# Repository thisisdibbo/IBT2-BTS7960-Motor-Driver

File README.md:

# IBT-2 High-Current H-Bridge Motor Driver (BTS7960B) — Custom PCB

A custom-designed **IBT-2 style H-bridge motor driver** built around two Infineon **BTS7960B** high-current half-bridges and a **TI SN74HC244** input buffer. It drives one brushed DC motor in both directions, with PWM speed control from any microcontroller (Arduino, ESP32, STM32, …).

The board was designed in Autodesk EAGLE, then fabricated, assembled and bench-tested: **at full drive, the voltage across the motor terminals equals the supply voltage**, confirming that the H-bridge switches the full supply onto the load.

It also has a **built-in HAT circuit**: a red power LED, two green signal LEDs and a 4-pin JST connector that plugs straight into an Arduino shield PCB — see [Built-in HAT Circuit](#built-in-hat-circuit).

## Contents

- [Fabricated Board](#fabricated-board)
- [Schematic and PCB](#schematic-and-pcb)
- [Features](#features)
- [Built-in HAT Circuit](#built-in-hat-circuit)
- [How It Works](#how-it-works)
- [Pinout](#pinout)
- [Control Logic](#control-logic)
- [Quick Start (Arduino)](#quick-start-arduino)
- [Specifications](#specifications)
- [Test Results](#test-results)
- [Bill of Materials](#bill-of-materials)
- [Repository Structure](#repository-structure)
- [Limitations and Future Improvements](#limitations-and-future-improvements)
- [References](#references)
- [Author](#author)
- [License](#license)

---

## Fabricated Board

<!-- Put your two photos in the images/ folder with exactly these names: fabricated_1.jpg and fabricated_2.jpg -->
<p align="center">
  
  &nbsp;&nbsp;
  
</p>
<p align="center"><em>The fabricated and assembled board</em></p>

## Schematic and PCB

<p align="center"><em>Schematic — U4 buffers the inputs, U2 + U3 form the H-bridge, J1 = power in, J2 = motor out</em></p>

<p align="center"><em>PCB layout — 2 layers, 59.6 × 52.3 mm, red = top copper, blue = bottom copper, GND pour on both layers</em></p>

## Features

- **Full H-bridge** from two BTS7960B NovalithIC™ half-bridges (7 mΩ high-side + 9 mΩ low-side, typ.)
- **Buffered inputs** — an SN74HC244 sits between the microcontroller and the power stage
- **Only two control signals** (RPWM, LPWM) — both half-bridges are enabled automatically when logic power is present
- **Safe default state** — on-board 30 kΩ pull-downs hold RPWM/LPWM LOW if the MCU pins float (e.g. during reset), so the motor is held in brake instead of running
- **Built-in HAT circuit** — red power LED, two green signal LEDs and a 4-pin JST connector for direct connection to an Arduino shield PCB
- **Protection built into the BTS7960B** — current limitation, short-circuit and over-temperature shutdown, under-voltage shutdown, over-voltage lock-out
- **Adjustable slew rate** through the SR resistors (10 kΩ fitted)
- **Bulk capacitor** on the motor supply and a decoupling capacitor on the logic supply
- **5 mm screw terminals** for power and motor
- 4 × Ø3 mm mounting holes

## Built-in HAT Circuit

The logic side of the board is a small built-in **HAT circuit**: the driver plugs into an Arduino shield PCB with one cable, and its status can be read at a glance — no loose jumper wires.

| Part | Type | Function |
|:---:|:---|:---|
| LD1 | 🔴 Red LED, 3 mm | **Power ON** — lights when the logic supply (VCC) is present |
| R1 | Diode (on the R1 footprint) | **Reverse protection** — in series with the red power LED, protects the LED branch if VCC is connected backwards |
| LD2 | 🟢 Green LED, 3 mm | **RPWM signal** — lights when RPWM is HIGH (forward) |
| LD3 | 🟢 Green LED, 3 mm | **LPWM signal** — lights when LPWM is HIGH (reverse) |
| X1 | 4-pin JST connector | **Direct connection to the Arduino shield PCB** with a single JST cable (VCC, LPWM, RPWM, GND) |

The green LEDs are driven by the control signals themselves, so under PWM their brightness follows the duty cycle — direction and approximate speed are visible at a glance.

## How It Works

```mermaid
flowchart LR
    MCU["Arduino shield PCB<br/>or any MCU"] -->|RPWM, LPWM| X1["HAT circuit<br/>JST connector + LEDs"]
    X1 --> BUF["U4 · SN74HC244<br/>input buffer"]
    BUF -->|IN, INH| U2["U2 · BTS7960B<br/>half-bridge A"]
    BUF -->|IN, INH| U3["U3 · BTS7960B<br/>half-bridge B"]
    PSU["Motor supply<br/>B+ / B−"] --> U2
    PSU --> U3
    U2 -->|M+| MOT(("DC<br/>motor"))
    U3 -->|M−| MOT
```

- **Power stage** — each BTS7960B contains a high-side P-MOSFET, a low-side N-MOSFET and a gate driver with built-in dead-time. With INH HIGH, `IN = HIGH` connects the output to B+ and `IN = LOW` connects it to GND; INH LOW puts the chip to sleep. U2 drives **M+**, U3 drives **M−**, and the motor sits between them.
- **Input stage** — U4 buffers RPWM → U2 `IN` and LPWM → U3 `IN`. Two more U4 channels (1A2, 1A4) are tied to VCC, so both `INH` pins go HIGH as soon as logic power is applied. The unused second half of U4 has its inputs and output-enable tied to GND so nothing floats.
- **Slew rate and current sense** — R9/R11 (10 kΩ, SR → GND) give a moderate switching slew rate. The IS (current-sense / fault) pins are terminated with R10/R12 (10 kΩ) to GND and are not routed to the header in this revision.
- **Supply** — C2 (330 µF) is the bulk capacitor on B+, C1 (100 nF) decouples U4. A diode on the R1 footprint sits in series with the power-LED branch (X1-1 → R1 → R2 → LD1). Logic ground and power ground are the same net.

## Pinout

> The **B+ B− M+ M−** labels are printed on the **bottom** silkscreen. On X1, pin 4 (GND) is next to the **GND** mark on the top silkscreen.

### X1 — JST logic connector (4-pin, to the Arduino shield)

| Pin | Signal | Description |
|:---:|:---|:---|
| 1 | **VCC** | Logic supply for U4 — 5 V (or 3.3 V for 3.3 V MCUs). Also enables both half-bridges; red LED LD1 lights. |
| 2 | **LPWM** | Drives U3 → **M−**. HIGH = M− to B+, LOW = M− to GND. Green LED: LD3 |
| 3 | **RPWM** | Drives U2 → **M+**. HIGH = M+ to B+, LOW = M+ to GND. Green LED: LD2 |
| 4 | **GND** | Ground (same net as B−) |

### J1 — Power input (2-pin screw terminal, 5 mm)

| Pin | Label | Description |
|:---:|:---:|:---|
| 1 | **B+** | Motor supply V<sub>S</sub>, 5.5 – 27.5 V |
| 2 | **B−** | Supply ground |

### J2 — Motor output (2-pin screw terminal, 5 mm)

| Pin | Label | Description |
|:---:|:---:|:---|
| 1 | **M+** | Output of U2 (controlled by RPWM) |
| 2 | **M−** | Output of U3 (controlled by LPWM) |

> **Wiring:** always connect the microcontroller GND to X1-4. B− and X1-4 are the same ground.

## Control Logic

Both half-bridges are enabled whenever VCC is present (INH = HIGH).

| RPWM (X1-3) | LPWM (X1-2) | M+ | M− | Motor |
|:---:|:---:|:---:|:---:|:---|
| HIGH | LOW | B+ | GND | Forward, full speed (V<sub>out</sub> ≈ V<sub>in</sub>) |
| LOW | HIGH | GND | B+ | Reverse, full speed |
| PWM | LOW | PWM | GND | Forward, speed ∝ duty cycle |
| LOW | PWM | GND | PWM | Reverse, speed ∝ duty cycle |
| LOW | LOW | GND | GND | Brake (both low-side switches on) — also the default when the inputs float |
| HIGH | HIGH | B+ | B+ | Brake (both high-side switches on) |

> Bring the motor to a stop (both inputs LOW) before reversing direction.

## Quick Start (Arduino)

Plug the JST cable from the Arduino shield PCB into X1, or wire the pins directly:

| Driver | Connect to |
|:---|:---|
| X1-1 VCC | Arduino **5V** |
| X1-2 LPWM | Arduino **D6** |
| X1-3 RPWM | Arduino **D5** |
| X1-4 GND | Arduino **GND** |
| J1 B+ / B− | Motor power supply + / − |
| J2 M+ / M− | DC motor |

```cpp
// IBT-2 (BTS7960B) custom driver — bidirectional test
const uint8_t RPWM = 5;   // X1-3 -> M+
const uint8_t LPWM = 6;   // X1-2 -> M-

// speed: -255 (full reverse) ... 0 (brake) ... +255 (full forward)
void setMotor(int speed) {
  speed = constrain(speed, -255, 255);
  if (speed >= 0) {
    analogWrite(LPWM, 0);
    analogWrite(RPWM, speed);
  } else {
    analogWrite(RPWM, 0);
    analogWrite(LPWM, -speed);
  }
}

void setup() {
  pinMode(RPWM, OUTPUT);
  pinMode(LPWM, OUTPUT);
  setMotor(0);
}

void loop() {
  setMotor(255);  delay(2000);   // full forward: V(M+ - M-) ≈ +V_in
  setMotor(0);    delay(1000);   // brake
  setMotor(-255); delay(2000);   // full reverse: V(M+ - M-) ≈ -V_in
  setMotor(0);    delay(1000);
  setMotor(128);  delay(2000);   // about 50 % speed forward
  setMotor(0);    delay(1000);
}
```

**Notes**

- **3.3 V boards (ESP32, STM32, Pico):** power X1-1 (VCC) from **3.3 V**, not 5 V. With VCC = 5 V the 74HC244 needs about 3.5 V for a logic HIGH, which a 3.3 V pin may not reach reliably. The BTS7960B inputs only need ≥ 2.15 V, so 3.3 V logic is enough. *(3.3 V operation follows from the datasheets; not yet tested on this board.)*
- **Never power VCC above 5.3 V** — U4 passes VCC straight to the BTS7960B `IN`/`INH` pins, whose absolute maximum is 5.3 V.
- Arduino Uno PWM on D5/D6 runs at about 980 Hz, which can make the motor whine. The BTS7960B supports PWM up to 25 kHz.

## Specifications

| Parameter | Value |
|:---|:---|
| Motor supply V<sub>S</sub> (B+) | 5.5 – 27.5 V (BTS7960B operating range; undervoltage shutdown at 4.0 – 5.4 V, over-voltage lock-out at 27.6 – 30 V) |
| Logic supply (VCC) | 5 V nominal, 3.3 V for 3.3 V MCUs — max 5.3 V |
| Control inputs | RPWM, LPWM — active HIGH, 30 kΩ pull-down on each |
| Interface (HAT circuit) | 4-pin JST connector · red power LED · 2 green signal LEDs |
| PWM frequency | Up to 25 kHz |
| Switch on-resistance | 7 mΩ high-side + 9 mΩ low-side (typ. at 25 °C) → 16 mΩ path resistance |
| IC current limit | 43 A typ. — *board current is limited by the copper, see [Limitations](#limitations-and-future-improvements)* |
| Protection | Current limitation, short-circuit, over-temperature (latched), under-/over-voltage |
| PCB | 2 layers, 59.6 × 52.3 mm, 35 µm (1 oz) copper, GND pour on top and bottom |
| Trace widths | Signals 0.51 mm · V<sub>S</sub> 0.76–0.81 mm · motor outputs 1.27 mm |
| Mounting | 4 × Ø3.0 mm holes |
| Design tool | Autodesk EAGLE 9.6.2 |

## Test Results

| Test | Condition | Result |
|:---|:---|:---|
| Output voltage at full drive | Motor supply on B+/B−, logic powered, one input HIGH and the other LOW | V<sub>M+ − M−</sub> = V<sub>in</sub> ✅ |

<!-- Add your measured numbers here, e.g. "12.0 V in -> 12.0 V out", plus the motor or load used. -->

The output matched the supply, which means the high-side switch of one BTS7960B and the low-side switch of the other are fully on. The only loss is the typical 16 mΩ path resistance (≈ 16 mV per amp of motor current).

## Bill of Materials

| Ref | Qty | Value / Part | Package | Function |
|:---|:---:|:---|:---|:---|
| U2, U3 | 2 | Infineon **BTS7960B** | P-TO-263-7 | High-current half-bridge |
| U4 | 1 | TI **SN74HC244DW** | SOIC-20 (wide) | Octal buffer, input stage |
| R9, R11 | 2 | 10 kΩ (103) | 1206 | Slew-rate resistor, SR → GND |
| R10, R12 | 2 | 10 kΩ (103) | 1206 | Current-sense load, IS → GND |
| R5, R8 | 2 | 30 kΩ (303) | 1206 | Pull-downs on RPWM / LPWM |
| R6, R7 | 2 | 30 kΩ (303) | 1206 | Pull-downs on U4 enable inputs (tied to VCC in this revision, so optional) |
| R1 | 1 | Diode (fitted on the R1 footprint) | THT, 7.62 mm pitch | Reverse-polarity protection for the power-LED branch (X1-1 → R1 → R2 → LD1) |
| R2, R3, R4 | 3 | 1 kΩ | THT 0207, 7.62 mm pitch | LED series resistors: R2 → LD1 (red), R3 → LD2 (green), R4 → LD3 (green) |
| LD1 | 1 | Red LED, 3 mm | THT | Power indicator (HAT circuit) |
| LD2, LD3 | 2 | Green LED, 3 mm | THT | RPWM / LPWM signal indicators (HAT circuit) |
| C1 | 1 | 100 nF ceramic (X7R, ≥ 16 V) | 1206 | U4 supply decoupling |
| C2 | 1 | 330 µF electrolytic | Radial, 5 mm pitch, up to Ø10 mm | Motor-supply bulk capacitor — voltage rating must be above B+ (e.g. 35 V for a 24 V supply) |
| X1 | 1 | 4-pin JST connector | 2.54 mm pitch (Molex 22-23-2041 footprint) | Logic connector to the Arduino shield (HAT circuit) |
| J1, J2 | 2 | 2-pin PCB screw terminal | 5 mm pitch | Power input / motor output |

> The BTS7960B is listed as obsolete by major distributors (e.g. DigiKey) — check availability before building one.

## Repository Structure

```
IBT2-BTS7960-Motor-Driver/
├── hardware/
│   ├── IBT2_BTS7960.sch            # EAGLE schematic
│   ├── IBT2_BTS7960.brd            # EAGLE board layout
│   └── IBT2_BTS7960.dxf            # DXF export (top copper, pads, vias, outline)
├── fabrication/
│   ├── board_print_2025-07-05.pdf  # 1:1 board print, A4
│   └── board_print_2025-07-06.pdf  # 1:1 board print, A4
├── images/
│   ├── schematic.png
│   ├── pcb_layout.png
│   ├── fabricated_1.jpg
│   └── fabricated_2.jpg
├── LICENSE
└── README.md
```

Open the `.sch` / `.brd` pair in **Autodesk EAGLE 9.x** or **Autodesk Fusion Electronics**; KiCad can also import EAGLE projects. Keep both files in the same folder with the same name so the schematic and board stay linked.

## Limitations and Future Improvements

**Current capability.** The BTS7960B itself handles tens of amps, but on this PCB the motor current flows through 0.76 mm (V<sub>S</sub>) and 1.27 mm (output) traces on 1 oz copper, with single vias where the power paths change layers. A rough IPC-2221 estimate puts the V<sub>S</sub> trace at about **2 – 2.7 A continuous** (10 – 20 °C temperature rise). Use it with small-to-medium motors and check the trace temperature before running higher currents.

**Fault reset.** Because `INH` is tied HIGH through U4, a latched over-temperature or short-circuit shutdown is cleared by power-cycling VCC (this pulls `INH` LOW).

Planned for the next revision:

- [ ] Replace the V<sub>S</sub> and output traces with wide copper pours and stitching vias; add more copper under the BTS7960B tabs, or a heatsink
- [ ] Add a 470 nF ceramic capacitor from V<sub>S</sub> to GND next to each BTS7960B (recommended in the datasheet)
- [ ] Bring R_IS / L_IS (current sense and fault flag) to the header, with R<sub>IS</sub> ≈ 1 kΩ (≈ 1 V per 8.5 A)
- [ ] Bring R_EN / L_EN to the header so the MCU can disable the bridge and reset faults
- [ ] Add reverse-polarity protection on B+
- [ ] Move the reverse-protection diode (now on the R1 footprint) in series with the whole VCC input — today it protects only the power-LED branch, because U4 takes VCC directly from X1-1 (a Schottky diode keeps the drop low)

## References

- [Infineon BTS7960 datasheet](https://www.infineon.com/dgdl/Infineon-BTS7960-DS-v01_01-en.pdf)
- [TI SN74HC244 product page and datasheet](https://www.ti.com/product/SN74HC244)

## Author

**Md. Mahin Rahman** — [@thisisdibbo](https://github.com/thisisdibbo) · [mr.d2003feb@gmail.com](mailto:mr.d2003feb@gmail.com)<br>
Department of Electrical and Electronic Engineering, Islamic University of Technology (IUT), Gazipur, Bangladesh

## License

Released under the [MIT License](LICENSE).

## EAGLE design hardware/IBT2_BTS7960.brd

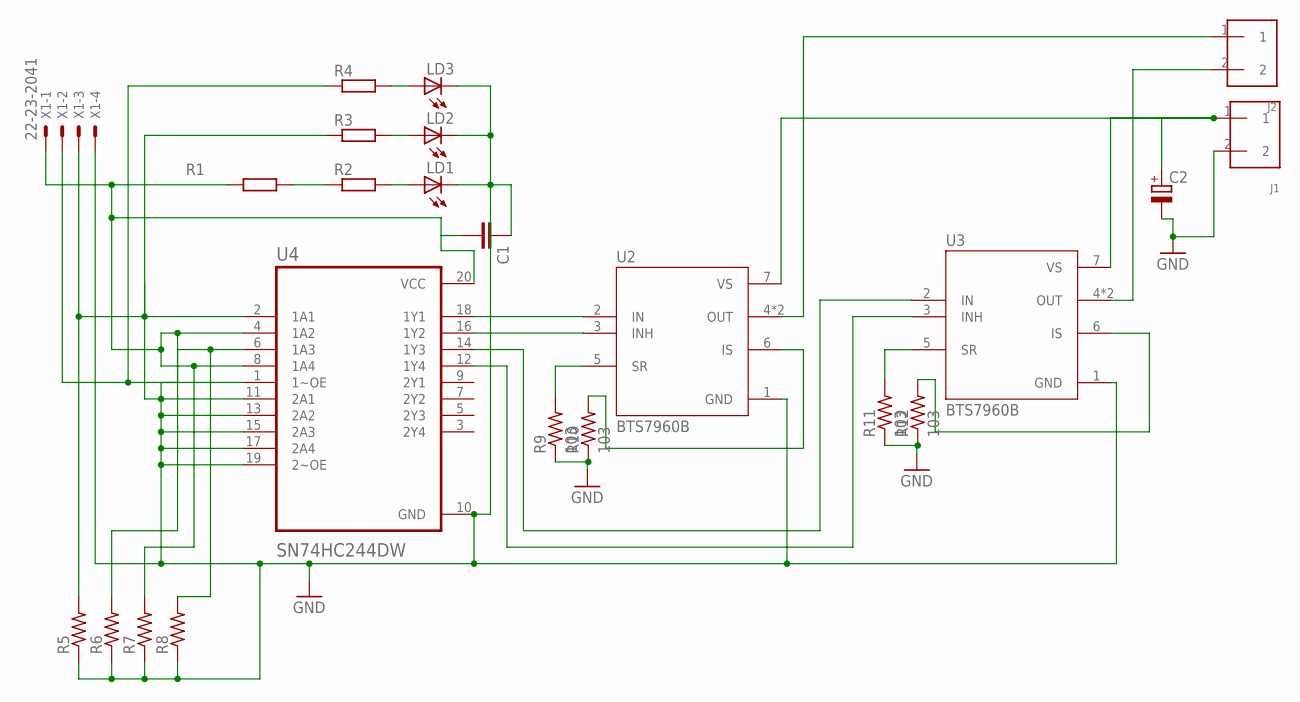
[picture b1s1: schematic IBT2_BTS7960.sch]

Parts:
C1: C-EUC1206K; C1206K
C2: CPOL-EUE5-10.5; E5-10,5
J1, J2: SCREW_TERMINAL; PHEONIX-1935161
LD1, LD2, LD3: LED3MM
R1, R2, R3, R4: R-EU_0207/7; 0207/7
R5, R6, R7, R8: R-US_M1206; M1206
R9, R10, R11, R12: 103; M1206
U2, U3: BTS7960B; DPAK127P1490X440-8N
U4: SN74HC244DW; SOIC127P1030X265-20N
X1: 22-23-2041

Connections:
GND: C1.1, C2.-, J1.2, LD1.K (C), LD2.K (C), LD3.K (C), R5.1, R6.1, R7.1, R8.1, R9.1, R10.1, R11.1, R12.1, U2.1 (GND), U3.1 (GND), U4.1 (1~OE), U4.10 (GND), U4.11 (2A1), U4.13 (2A2), U4.15 (2A3), U4.17 (2A4), U4.19 (2~OE), X1.4
unnamed: U2.2 (IN), U4.18 (1Y1)
unnamed: R1.2, R2.1
unnamed: LD1.A, R2.2
unnamed: C1.2, R1.1, R6.2, R7.2, U4.4 (1A2), U4.8 (1A4), U4.20 (VCC), X1.1
unnamed: R4.1, R8.2, U4.6 (1A3), X1.2
unnamed: R3.1, R5.2, U4.2 (1A1), X1.3
unnamed: LD2.A, R3.2
unnamed: LD3.A, R4.2
unnamed: U2.3 (INH), U4.16 (1Y2)
unnamed: R9.2, U2.5 (SR)
unnamed: R10.2, U2.6 (IS)
unnamed: U3.2 (IN), U4.14 (1Y3)
unnamed: U3.3 (INH), U4.12 (1Y4)
unnamed: R11.2, U3.5 (SR)
unnamed: R12.2, U3.6 (IS)
unnamed: C2.+, J1.1, U2.7 (VS), U3.7 (VS)
unnamed: J2.1, U2.4 (OUT), U2.8 (OUT)
unnamed: J2.2, U3.4 (OUT), U3.8 (OUT)

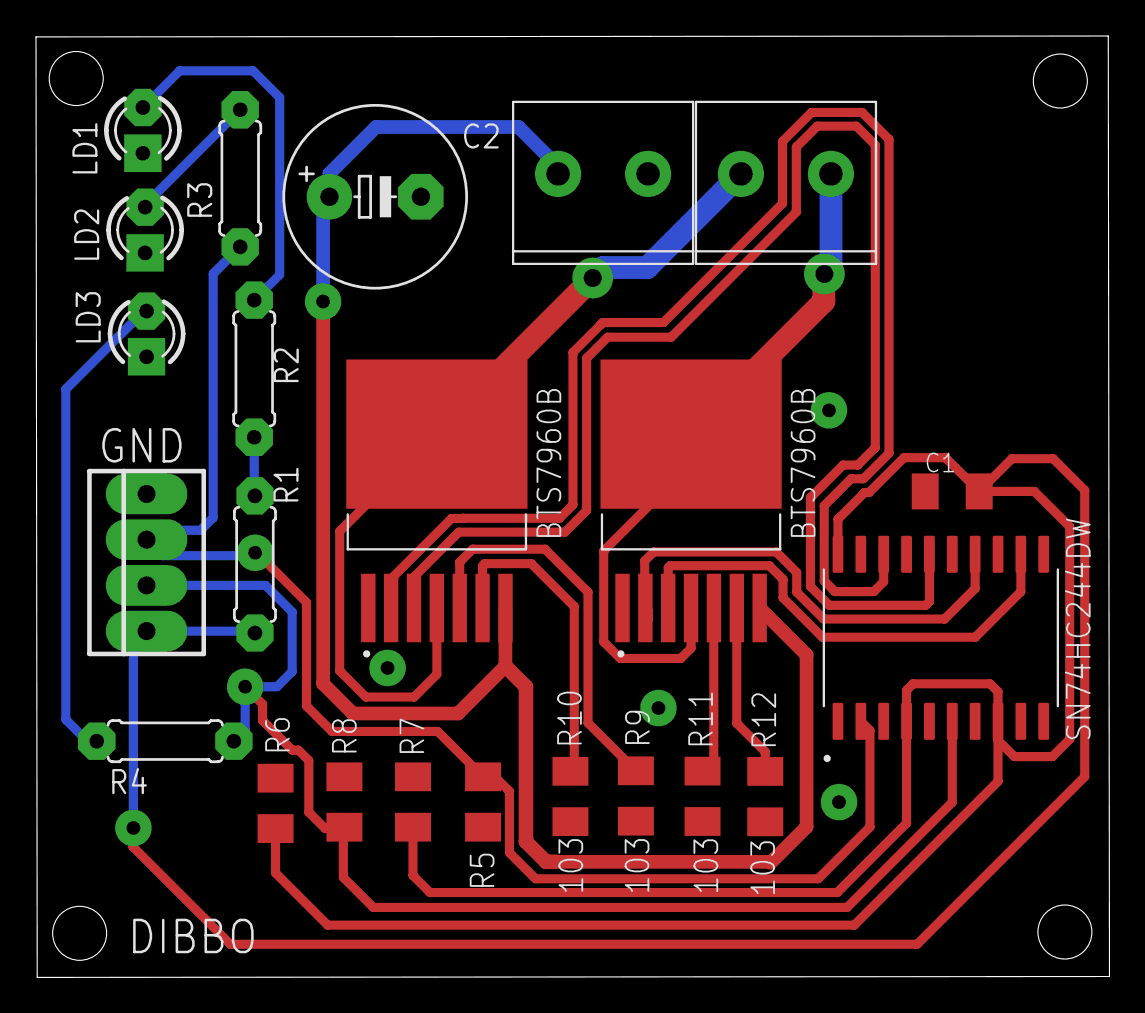
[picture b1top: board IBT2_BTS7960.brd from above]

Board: 2 copper layers, 59.6 x 52.3 mm, 23 parts (0 on the bottom side), 19 nets.

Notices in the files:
README.md:
License: MIT
